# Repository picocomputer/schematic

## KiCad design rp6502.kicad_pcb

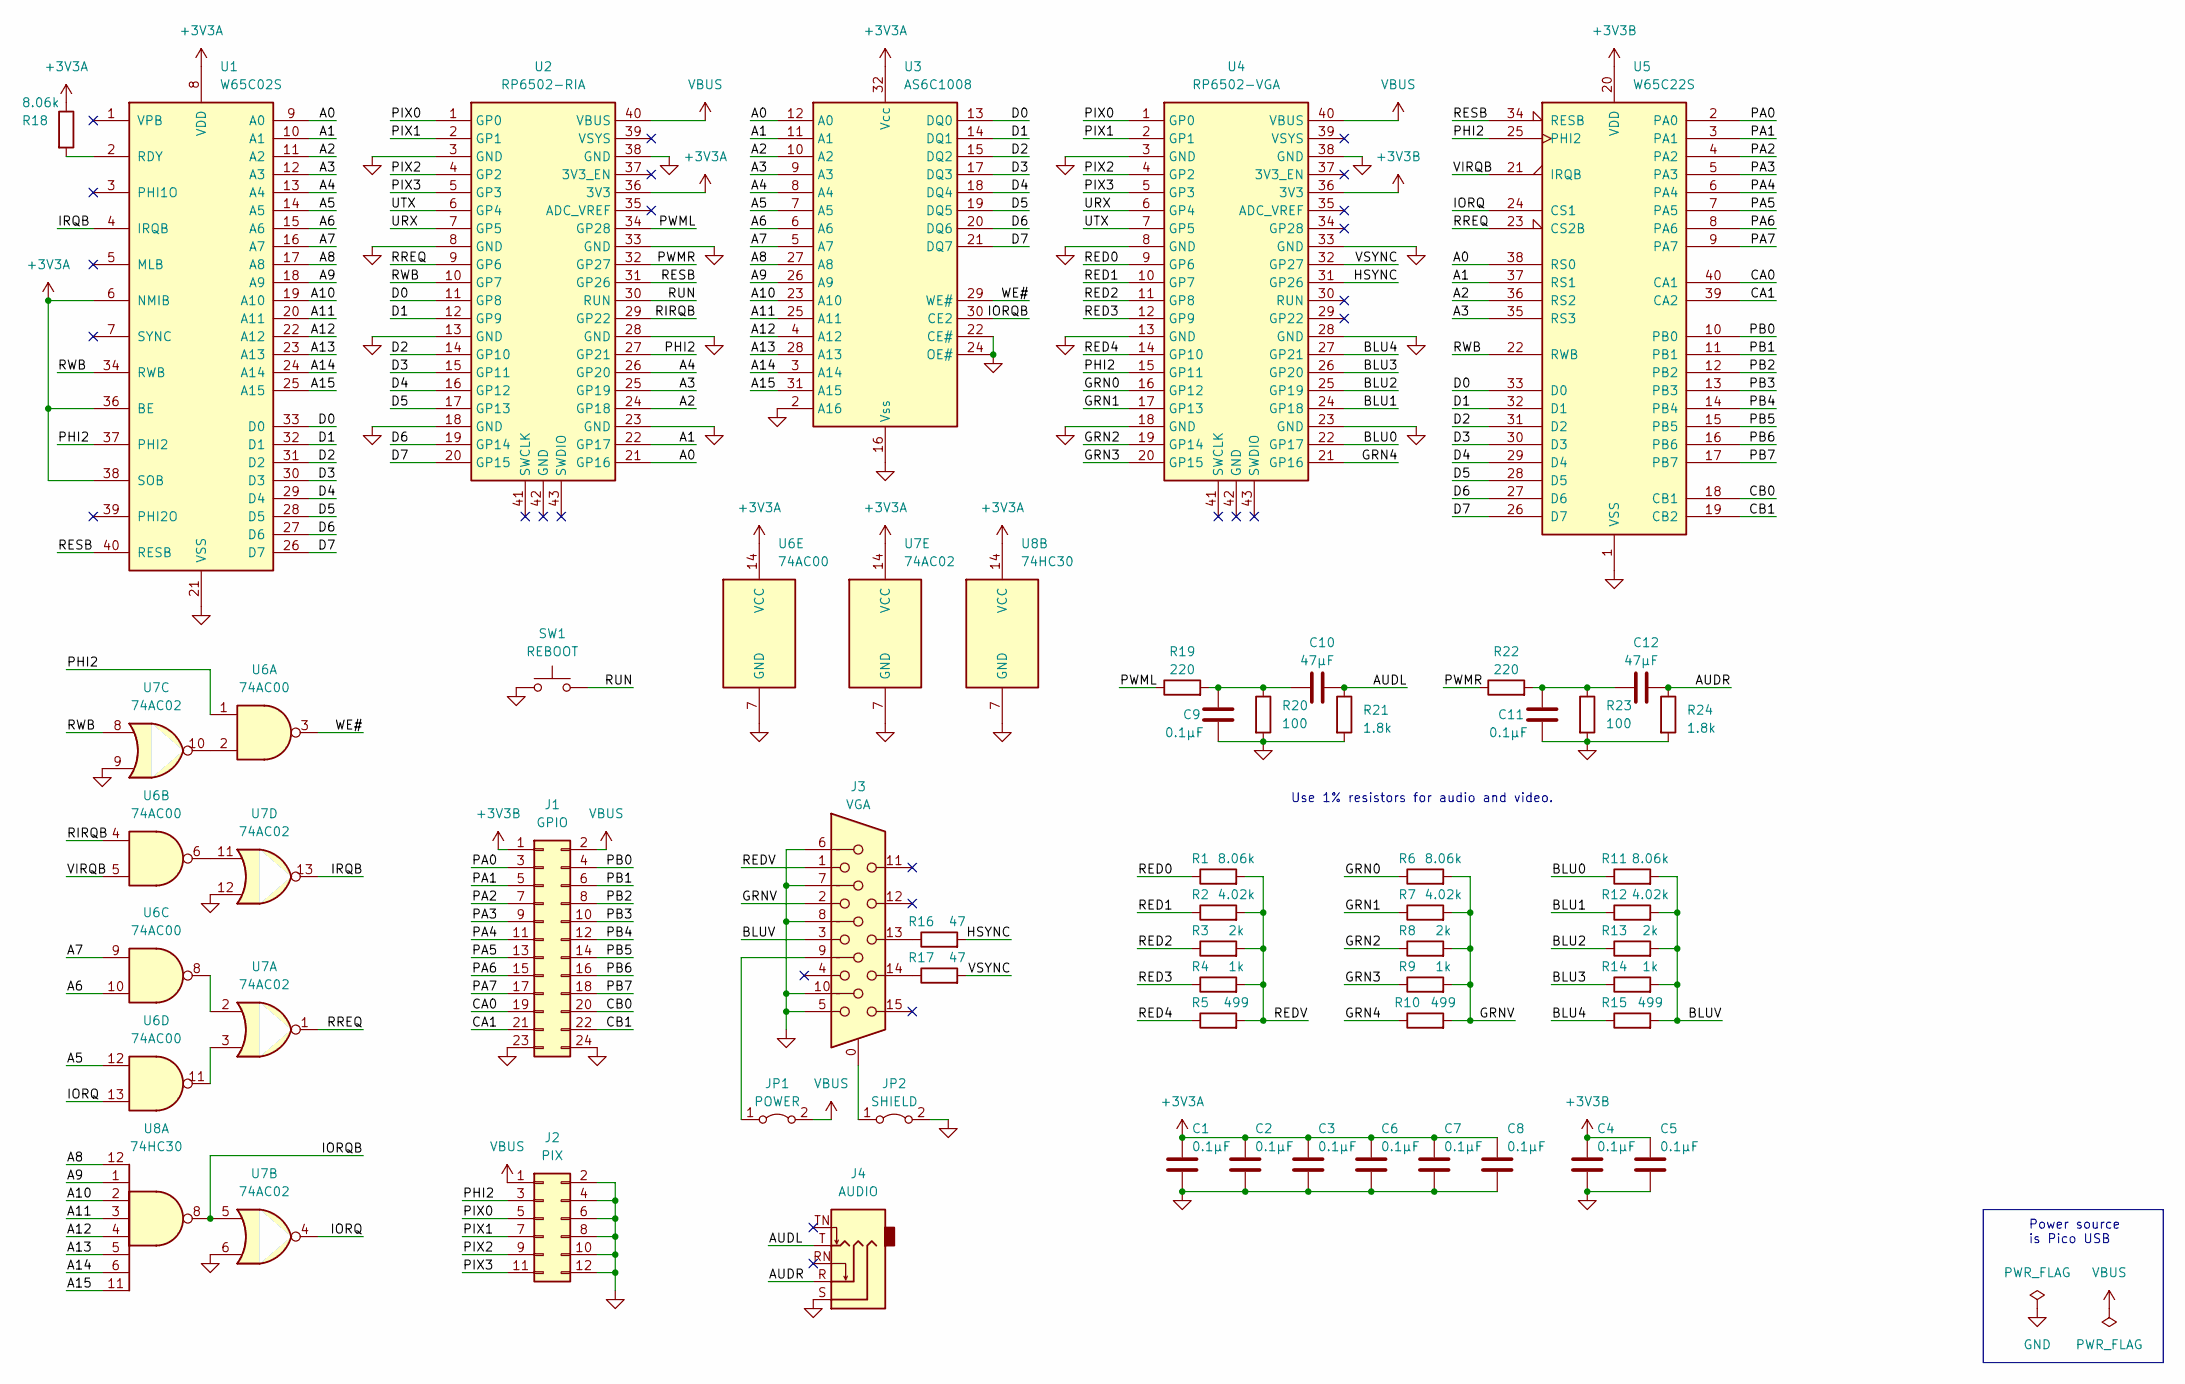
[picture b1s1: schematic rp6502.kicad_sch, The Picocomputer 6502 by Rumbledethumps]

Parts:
C1, C2, C3, C4, C5, C6, C7, C8, C9, C11: 0.1μF; R_Axial_DIN0207_L6.3mm_D2.5mm_P10.16mm_Horizontal_Long
C10, C12: 47μF; C_Disc_D7.5mm_W5.0mm_P5.00mm_Long
J1: GPIO; PinHeader_2x12_P2.54mm_Vertical
J2: PIX; PinHeader_2x06_P2.54mm_Vertical
J3: VGA; DSUB-15-HD_Female_Horizontal_P2.29x2.54mm_EdgePinOffset8.35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
J4: AUDIO; Jack_3.5mm_CUI_SJ1-3525N_Horizontal
JP1: POWER; SolderJumper-2_P1.3mm_Bridged2Bar_RoundedPad1.0x1.5mm
JP2: SHIELD; SolderJumper-2_P1.3mm_Bridged2Bar_RoundedPad1.0x1.5mm
R1, R6, R11, R18: 8.06k; R_Axial_DIN0207_L6.3mm_D2.5mm_P10.16mm_Horizontal_Long
R2, R7, R12: 4.02k; R_Axial_DIN0207_L6.3mm_D2.5mm_P10.16mm_Horizontal_Long
R3, R8, R13: 2k; R_Axial_DIN0207_L6.3mm_D2.5mm_P10.16mm_Horizontal_Long
R4, R9, R14: 1k; R_Axial_DIN0207_L6.3mm_D2.5mm_P10.16mm_Horizontal_Long
R5, R10, R15: 499; R_Axial_DIN0207_L6.3mm_D2.5mm_P10.16mm_Horizontal_Long
R16, R17: 47; R_Axial_DIN0207_L6.3mm_D2.5mm_P10.16mm_Horizontal_Long
R19, R22: 220; R_Axial_DIN0207_L6.3mm_D2.5mm_P10.16mm_Horizontal_Long
R20, R23: 100; R_Axial_DIN0207_L6.3mm_D2.5mm_P10.16mm_Horizontal_Long
R21, R24: 1.8k; R_Axial_DIN0207_L6.3mm_D2.5mm_P10.16mm_Horizontal_Long
SW1: REBOOT; SW_Tactile_SKHH_Angled
U1: W65C02S; DIP-40_W15.24mm_LongPads
U2: RP6502-RIA; DIP-40_W17.78mm_LongPads
U3: AS6C1008; DIP-32_W15.24mm_LongPads
U4: RP6502-VGA; DIP-40_W17.78mm_LongPads
U5: W65C22S; DIP-40_W15.24mm_LongPads
U6: 74AC00; DIP-14_W7.62mm_LongPads
U7: 74AC02; DIP-14_W7.62mm_LongPads
U8: 74HC30; DIP-14_W7.62mm_LongPads

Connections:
+3V3A: C1.1, C2.1, C3.1, C6.1, C7.1, C8.1, R18.1, U1.6 (NMIB), U1.8 (VDD), U1.36 (BE), U1.38 (SOB), U2.36 (3V3), U3.32 (Vcc), U6.14 (VCC), U7.14 (VCC), U8.14 (VCC)
+3V3B: C4.1, C5.1, J1.1, U4.36 (3V3), U5.20 (VDD)
/A0: U1.9 (A0), U2.21 (GP16), U3.12 (A0), U5.38 (RS0)
/A1: U1.10 (A1), U2.22 (GP17), U3.11 (A1), U5.37 (RS1)
/A2: U1.11 (A2), U2.24 (GP18), U3.10 (A2), U5.36 (RS2)
/A3: U1.12 (A3), U2.25 (GP19), U3.9 (A3), U5.35 (RS3)
/A4: U1.13 (A4), U2.26 (GP20), U3.8 (A4)
/A5: U1.14 (A5), U3.7 (A5), U6.12
/A6: U1.15 (A6), U3.6 (A6), U6.10
/A7: U1.16 (A7), U3.5 (A7), U6.9
/A8: U1.17 (A8), U3.27 (A8), U8.12
/A9: U1.18 (A9), U3.26 (A9), U8.1
/A10: U1.19 (A10), U3.23 (A10), U8.2
/A11: U1.20 (A11), U3.25 (A11), U8.3
/A12: U1.22 (A12), U3.4 (A12), U8.4
/A13: U1.23 (A13), U3.28 (A13), U8.5
/A14: U1.24 (A14), U3.3 (A14), U8.6
/A15: U1.25 (A15), U3.31 (A15), U8.11
/AUDL: C10.2, J4.T, R21.1
/AUDR: C12.2, J4.R, R24.1
/BLU0: R11.1, U4.22 (GP17)
/BLU1: R12.1, U4.24 (GP18)
/BLU2: R13.1, U4.25 (GP19)
/BLU3: R14.1, U4.26 (GP20)
/BLU4: R15.1, U4.27 (GP21)
/BLUV: J3.3, R11.2, R12.2, R13.2, R14.2, R15.2
/CA0: J1.19, U5.40 (CA1)
/CA1: J1.21, U5.39 (CA2)
/CB0: J1.20, U5.18 (CB1)
/CB1: J1.22, U5.19 (CB2)
/D0: U1.33 (D0), U2.11 (GP8), U3.13 (DQ0), U5.33 (D0)
/D1: U1.32 (D1), U2.12 (GP9), U3.14 (DQ1), U5.32 (D1)
/D2: U1.31 (D2), U2.14 (GP10), U3.15 (DQ2), U5.31 (D2)
/D3: U1.30 (D3), U2.15 (GP11), U3.17 (DQ3), U5.30 (D3)
/D4: U1.29 (D4), U2.16 (GP12), U3.18 (DQ4), U5.29 (D4)
/D5: U1.28 (D5), U2.17 (GP13), U3.19 (DQ5), U5.28 (D5)
/D6: U1.27 (D6), U2.19 (GP14), U3.20 (DQ6), U5.27 (D6)
/D7: U1.26 (D7), U2.20 (GP15), U3.21 (DQ7), U5.26 (D7)
/GRN0: R6.1, U4.16 (GP12)
/GRN1: R7.1, U4.17 (GP13)
/GRN2: R8.1, U4.19 (GP14)
/GRN3: R9.1, U4.20 (GP15)
/GRN4: R10.1, U4.21 (GP16)
/GRNV: J3.2, R6.2, R7.2, R8.2, R9.2, R10.2
/HSYNC: R16.2, U4.31 (GP26)
/IORQ: U5.24 (CS1), U6.13, U7.4
/IORQB: U3.30 (CE2), U7.5, U8.8
/IRQB: U1.4 (IRQB), U7.13
/PA0: J1.3, U5.2 (PA0)
/PA1: J1.5, U5.3 (PA1)
/PA2: J1.7, U5.4 (PA2)
/PA3: J1.9, U5.5 (PA3)
/PA4: J1.11, U5.6 (PA4)
/PA5: J1.13, U5.7 (PA5)
/PA6: J1.15, U5.8 (PA6)
/PA7: J1.17, U5.9 (PA7)
/PB0: J1.4, U5.10 (PB0)
/PB1: J1.6, U5.11 (PB1)
/PB2: J1.8, U5.12 (PB2)
/PB3: J1.10, U5.13 (PB3)
/PB4: J1.12, U5.14 (PB4)
/PB5: J1.14, U5.15 (PB5)
/PB6: J1.16, U5.16 (PB6)
/PB7: J1.18, U5.17 (PB7)
/PHI2: J2.3, U1.37 (PHI2), U2.27 (GP21), U4.15 (GP11), U5.25 (PHI2), U6.1
/PIX0: J2.5, U2.1 (GP0), U4.1 (GP0)
/PIX1: J2.7, U2.2 (GP1), U4.2 (GP1)
/PIX2: J2.9, U2.4 (GP2), U4.4 (GP2)
/PIX3: J2.11, U2.5 (GP3), U4.5 (GP3)
/PWML: R19.1, U2.34 (GP28)
/PWMR: R22.1, U2.32 (GP27)
/RED0: R1.1, U4.9 (GP6)
/RED1: R2.1, U4.10 (GP7)
/RED2: R3.1, U4.11 (GP8)
/RED3: R4.1, U4.12 (GP9)
/RED4: R5.1, U4.14 (GP10)
/REDV: J3.1, R1.2, R2.2, R3.2, R4.2, R5.2
/RESB: U1.40 (RESB), U2.31 (GP26), U5.34 (RESB)
/RIRQB: U2.29 (GP22), U6.4
/RREQ: U2.9 (GP6), U5.23 (CS2B), U7.1
/RUN: SW1.2, U2.30 (RUN)
/RWB: U1.34 (RWB), U2.10 (GP7), U5.22 (RWB), U7.8
/SWCLK: U4.29 (GP22)
/SWDIO: U4.34 (GP28)
/URX: U2.7 (GP5), U4.6 (GP4)
/UTX: U2.6 (GP4), U4.7 (GP5)
/VIRQB: U5.21 (IRQB), U6.5
/VSYNC: R17.2, U4.32 (GP27)
/WE#: U3.29 (WE#), U6.3
GND: C1.2, C2.2, C3.2, C4.2, C5.2, C6.2, C7.2, C8.2, C9.2, C11.2, J1.23, J1.24, J2.2, J2.4, J2.6, J2.8, J2.10, J2.12, J3.5, J3.6, J3.7, J3.8, J3.10, J4.S, JP2.2 (B), R20.2, R21.2, R23.2, R24.2, SW1.1, U1.21 (VSS), U2.3 (GND), U2.8 (GND), U2.13 (GND), U2.18 (GND), U2.23 (GND), U2.28 (GND), U2.33 (GND), U2.38 (GND), U3.2 (A16), U3.16 (Vss), U3.22 (CE#), U3.24 (OE#), U4.3 (GND), U4.8 (GND), U4.13 (GND), U4.18 (GND), U4.23 (GND), U4.28 (GND), U4.33 (GND), U4.38 (GND), U5.1 (VSS), U6.7 (GND), U7.6, U7.7 (GND), U7.9, U7.12, U8.7 (GND), U8.9 (NC)
unnamed: C9.1, C10.1, R19.2, R20.1
unnamed: C11.1, C12.1, R22.2, R23.1
unnamed: J3.13, R16.1
unnamed: J3.14, R17.1
unnamed: J3.9, JP1.1 (A)
unnamed: J3.0, JP2.1 (A)
unnamed: R18.2, U1.2 (RDY)
unnamed: U6.2, U7.10
unnamed: U6.6, U7.11
unnamed: U6.8, U7.2
unnamed: U6.11, U7.3
VBUS: J1.2, J2.1, JP1.2 (B), U2.40 (VBUS), U4.40 (VBUS)

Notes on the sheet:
Use 1% resistors for audio and video.
Power source is Pico USB

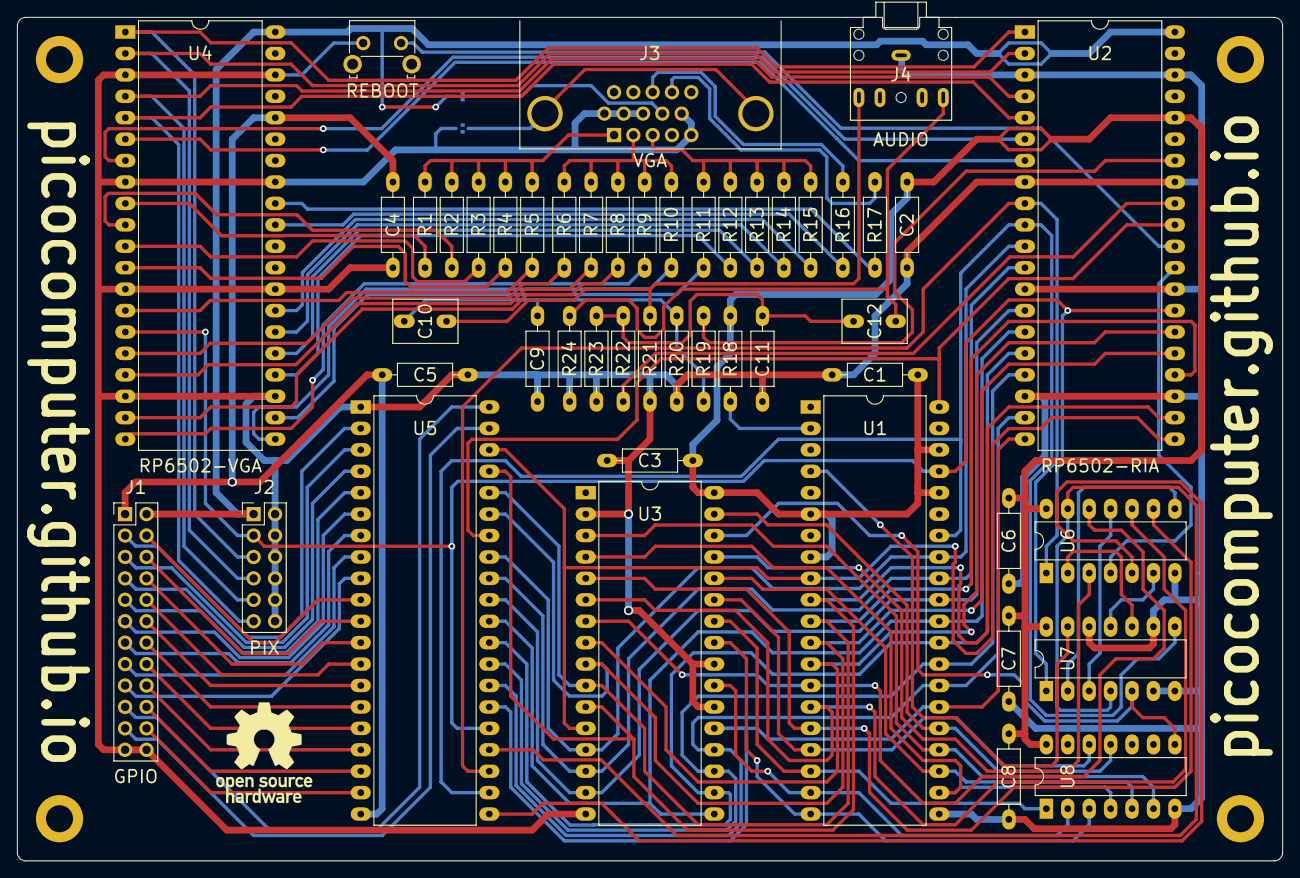
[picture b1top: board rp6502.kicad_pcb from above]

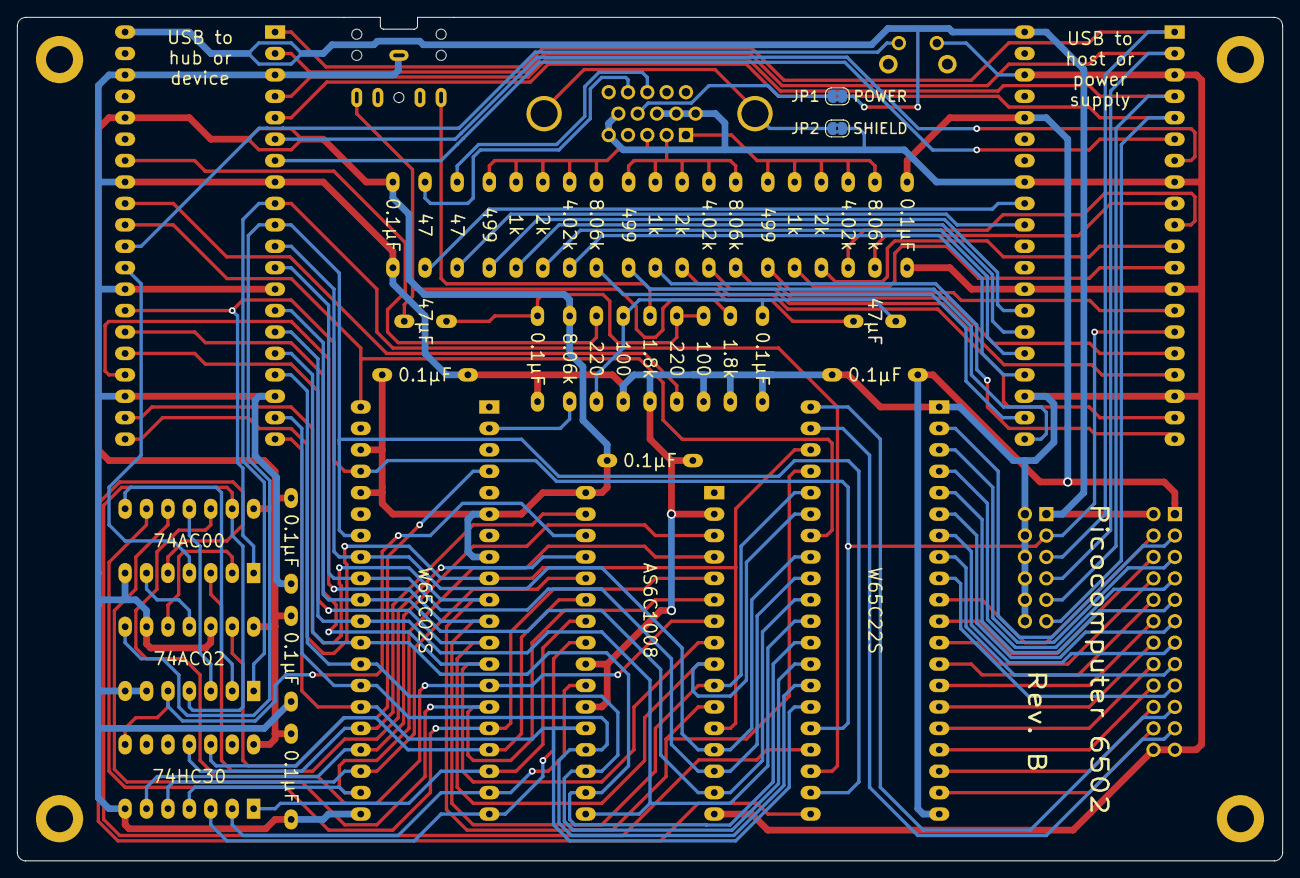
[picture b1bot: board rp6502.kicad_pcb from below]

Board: 2 copper layers, 150.0 x 100.0 mm, 51 parts (2 on the bottom side), 100 nets.

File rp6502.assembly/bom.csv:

Item#,Designator,Qty,Mfr Name,Mfr Part Number,Description,Mounting Type,Note
1,"C1-C9, C11",10,Vishay,A104M15X7RF5TAA,0.1uF Axial Ceramic Capacitor >=10V,"Through Hole, Axial",
2,"C10, C12",2,TDK,FG26X5R1E476MRT00,47uF Radial Ceramic Capacitor >=10V,"Through Hole, Radial",
3,"R1, R6, R11, R18",4,YAGEO,MFR-25FBF52-8K06,8.06k resistor 1%,"Through Hole, Axial",
4,"R2, R7, R12",3,YAGEO,MFR-25FBF52-4K02,4.02k resistor 1%,"Through Hole, Axial",
5,"R3, R8, R13",3,YAGEO,MFR-25FBF52-2K,2k resistor 1%,"Through Hole, Axial",
6,"R4, R9, R14",3,YAGEO,MFR-25FBF52-1K,1k resistor 1%,"Through Hole, Axial",
7,"R5, R10, R15",3,YAGEO,MFR-25FBF52-499R,499 ohm resistor 1%,"Through Hole, Axial",
8,"R16, R17",2,YAGEO,MFR-25FBF52-47R,47 ohm resistor 1%,"Through Hole, Axial",
9,"R19, R22",2,YAGEO,MFR-25FBF52-220R,220 ohm resistor 1%,"Through Hole, Axial",
10,"R20, R23",2,YAGEO,MFR-25FBF52-100R,100 ohm resistor 1%,"Through Hole, Axial",
11,"R21, R24",2,YAGEO,MFR-25FBF52-1K8,1.8k resistor 1%,"Through Hole, Axial",
12,J1,1,Amp,10129381-924001BLF,2x12 Pin Header,Through Hole,
13,J2,1,Amp,10129381-912001BLF,2x6 Pin Header,Through Hole,
14,J3,1,Amp,L77HDE15SD1CH4FVGA,VGA Jack,"Through Hole, Right",
15,J4,1,CUI,SJ1-3525NG-GR,Audio Jack,"Through Hole, Right",
16,REBOOT,1,CUI,TS11-674-43-BK-160-RA-D,Tactile Button,"Through Hole, Right",
17,"U1, U5",2,TE,1-2199299-5,40-pin IC Socket,Through Hole,
18,U3,1,TE,1-2199300-2,32-pin IC Socket,Through Hole,
19,"U6, U7, U8",3,TE,1-2199298-3,14-pin IC Socket,Through Hole,
20,"U2, U4",4,Wurth,61302011821,20 Pin Header Socket,Through Hole,Qty is correct. 2x for each.
21,U2,2,Adam Tech,RS1-03-G,3 Pin Header Socket,Through Hole,Qty is correct. 2x for U2 only.

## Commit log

2023-05-22 pcb beauty
2023-05-22 pcb complete
2023-05-23 founders edition
2023-06-08 update date
2023-06-22 first assembly
2023-06-27 PTH slot increase for PCBWay
2023-06-30 add standoffs
2023-06-30 update notes
2023-07-20 update assembly docs
2025-11-10 add drill guide
2025-11-14 fine tune acrylic
2026-01-27 revb
